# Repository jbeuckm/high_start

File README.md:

I2Cdev and MPU6050 libraries:
https://github.com/jrowberg/i2cdevlib/tree/master/Arduino

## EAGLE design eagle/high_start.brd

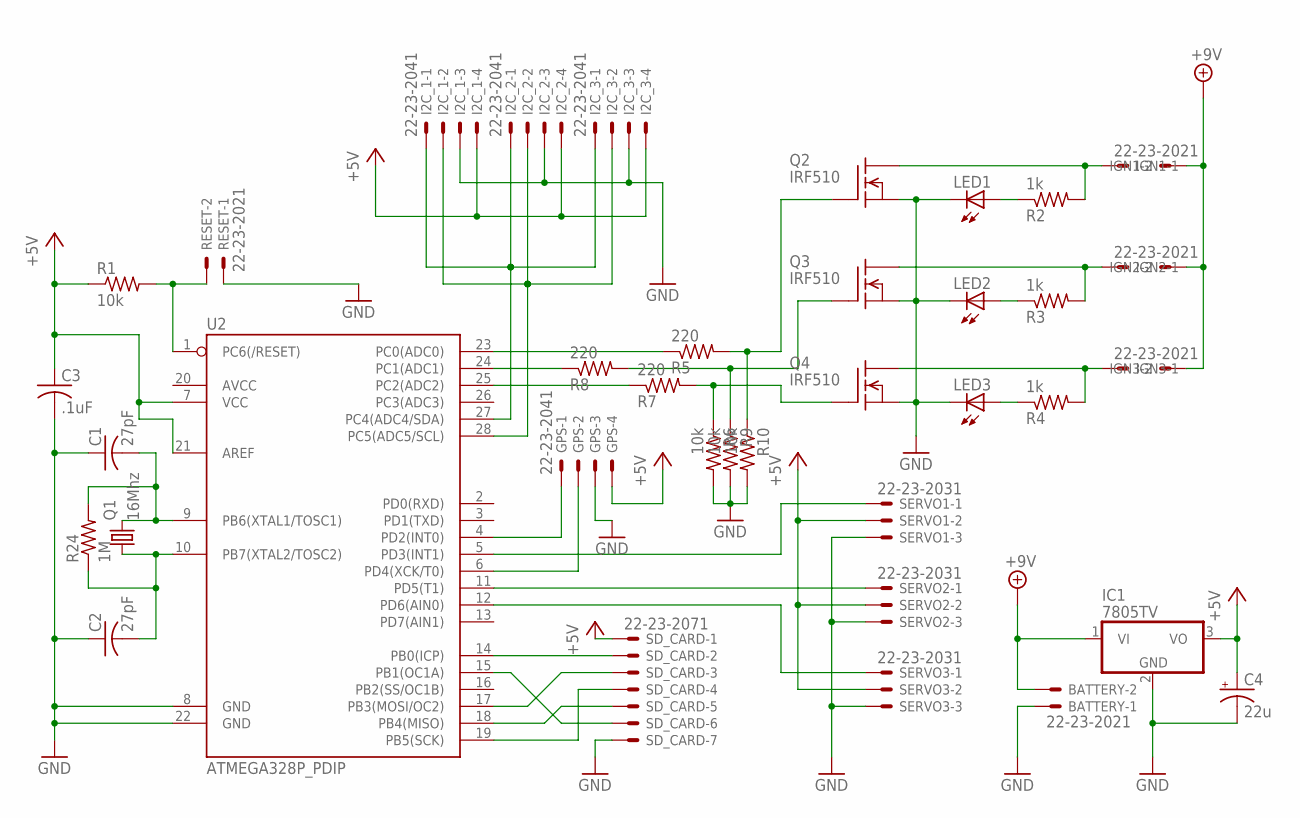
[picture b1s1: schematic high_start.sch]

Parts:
BATTERY: 22-23-2021
C1, C2: 27pF; C025-040X050
C3: .1uF; C025-030X050
C4: 22u; B45181A
GPS: 22-23-2041
I2C_1, I2C_2, I2C_3: 22-23-2041
IC1: 7805TV; TO220V
IGN1, IGN2, IGN3: 22-23-2021
LED1, LED2, LED3: LED5MM
Q1: 16Mhz; HC49/S
Q2, Q3, Q4: IRF510; TO220
R1: 10k; 0207/7
R2, R3, R4: 1k; 0207/7
R5, R7, R8: 220; 0207/7
R6, R9, R10: 10k; 0207/5V
R24: 1M; 0207/7
RESET: 22-23-2021
SD_CARD: 22-23-2071
SERVO1, SERVO2, SERVO3: 22-23-2031
U2: ATMEGA328P_PDIP; DIL28-3

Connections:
+5V: C3.1, C4.+, GPS.4, I2C_1.4, I2C_2.4, I2C_3.4, IC1.3 (VO), R1.1, SD_CARD.1, SERVO1.2, SERVO2.2, SERVO3.2, U2.7 (VCC), U2.21 (AREF)
+9V: BATTERY.2, IC1.1 (VI), IGN1.2, IGN2.2, IGN3.2
GND: BATTERY.1, C1.1, C2.1, C3.2, C4.-, GPS.3, I2C_1.3, I2C_2.3, I2C_3.3, IC1.2 (GND), LED1.K (C), LED2.K (C), LED3.K (C), Q2.3 (S), Q3.3 (S), Q4.3 (S), R6.2, R9.2, R10.2, RESET.1, SD_CARD.7, SERVO1.3, SERVO2.3, SERVO3.3, U2.8 (GND), U2.22 (GND)
unnamed: I2C_1.2, I2C_2.2, I2C_3.2, U2.28 (PC5(ADC5/SCL))
unnamed: I2C_1.1, I2C_2.1, I2C_3.1, U2.27 (PC4(ADC4/SDA))
unnamed: GPS.1, U2.4 (PD2(INT0))
unnamed: C1.2, Q1.2, R24.2, U2.9 (PB6(XTAL1/TOSC1))
unnamed: C2.2, Q1.1, R24.1, U2.10 (PB7(XTAL2/TOSC2))
unnamed: GPS.2, U2.6 (PD4(XCK/T0))
unnamed: SD_CARD.2, U2.14 (PB0(ICP))
unnamed: SD_CARD.3, U2.17 (PB3(MOSI/OC2))
unnamed: SD_CARD.4, U2.19 (PB5(SCK))
unnamed: SD_CARD.5, U2.18 (PB4(MISO))
unnamed: SD_CARD.6, U2.15 (PB1(OC1A))
unnamed: IGN1.1, Q2.2 (D), R2.2
unnamed: IGN2.1, Q3.2 (D), R3.2
unnamed: IGN3.1, Q4.2 (D), R4.2
unnamed: SERVO1.1, U2.5 (PD3(INT1))
unnamed: SERVO2.1, U2.11 (PD5(T1))
unnamed: SERVO3.1, U2.12 (PD6(AIN0))
unnamed: Q2.1 (G), R5.2, R10.1
unnamed: Q3.1 (G), R8.2, R9.1
unnamed: Q4.1 (G), R6.1, R7.2
unnamed: LED1.A, R2.1
unnamed: LED2.A, R3.1
unnamed: LED3.A, R4.1
unnamed: R5.1, U2.23 (PC0(ADC0))
unnamed: R7.1, U2.25 (PC2(ADC2))
unnamed: R8.1, U2.24 (PC1(ADC1))
unnamed: R1.2, RESET.2, U2.1 (PC6(/RESET))

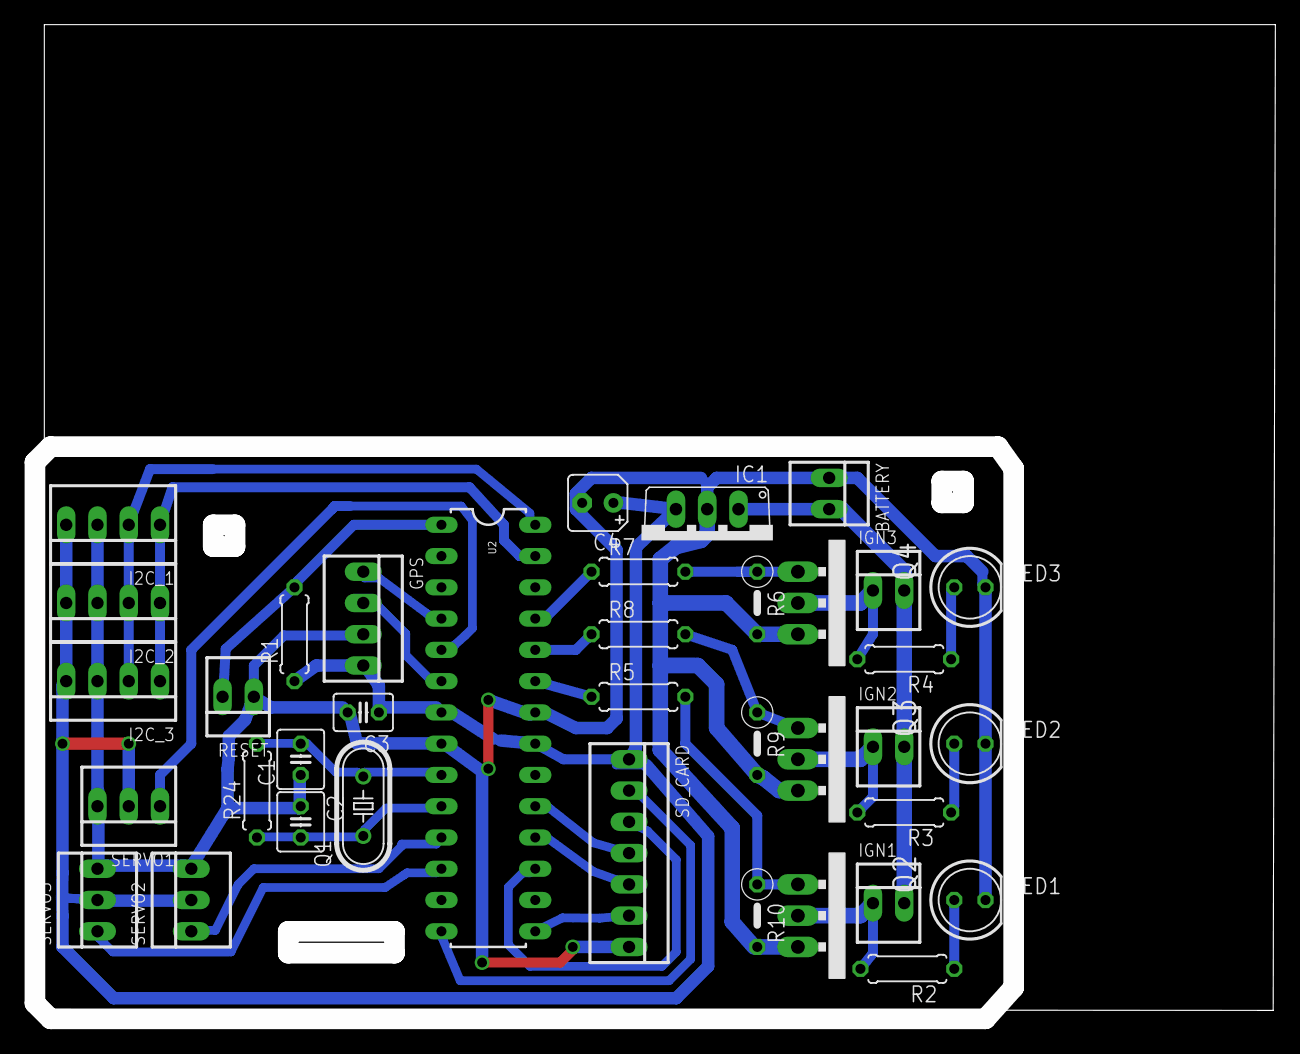
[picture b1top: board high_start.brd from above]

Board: 2 copper layers, 100.8 x 80.8 mm, 37 parts (0 on the bottom side), 30 nets.

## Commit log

2016-12-18 gyros are operating
2016-12-20 servo direct mapped to tilt
2016-12-23 logging acc and gyros to sd card
2016-12-23 readme tells where accelerometer libraries can be found
2016-12-23 flush datafile every row
2016-12-23 data picture from sdcard recorded by arduino
2016-12-23 wider, thinner, no tab at end of lines
2016-12-24 splitting up webapp
2016-12-24 splitting apart arduino functions and x axis zooms now
2016-12-24 zoom and pan x
2016-12-25 legend
2016-12-25 move lines instead of scale drawing
2016-12-25 threejs rotating cylinder
2016-12-25 threejs into a directive
2016-12-25 line chart into angular
2016-12-25 3js overlay
2016-12-25 PID connects acc directly to x y servos
2016-12-25 init pids
2016-12-25 running with no gps lib
2016-12-25 fixed tsv format
2016-12-25 greater ranges for acc and gyros
2016-12-26 setting file date
2016-12-27 saving bytes with short strings
2016-12-27 saving bytes putting strings into flash
2016-12-29 basic altimeter code
2016-12-31 nozzle pattern
2016-12-31 fixed alt code
2016-12-31 reading GPS at 1hz
2017-01-01 separated gps loop
2017-01-01 separate file for gps readings
2017-01-01 Zwriting millis in gps file
2017-01-01 writing gps file and state machine established
2017-01-03 pcb begins
2017-01-04 servo igniter altimeter gps and sd card connections
2017-01-04 tied led cathodes to gnd
2017-01-04 added battery and reg and layed out board
2017-01-04 moved power connector between fets and micro
2017-01-04 routed
2017-01-04 milling on board
2017-01-04 board tweaks and three servos into code
2017-01-06 added airframe cam files to the repo
2017-01-10 gcode
2017-01-12 wrote sd card from board
2017-01-14 pulldown resistors onto schemo
2017-01-14 pulldowns placed
2017-01-15 moved fets up to Vbatt for igniter5 worky
2017-01-19 generating flowchart with mermaid
2017-02-25 moved igniter FETs to low side
2017-03-16 janky rerouted
2017-03-16 improved reroute

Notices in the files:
parts and their libraries:
SparkFun-DigitalIC: Licensing: Creative Commons ShareAlike 4.0 International - https://creativecommons.org/licenses/by-sa/4.0
